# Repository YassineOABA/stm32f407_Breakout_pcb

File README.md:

# stm32f407_Breakout_pcb
HW PCB design based on STM32F407

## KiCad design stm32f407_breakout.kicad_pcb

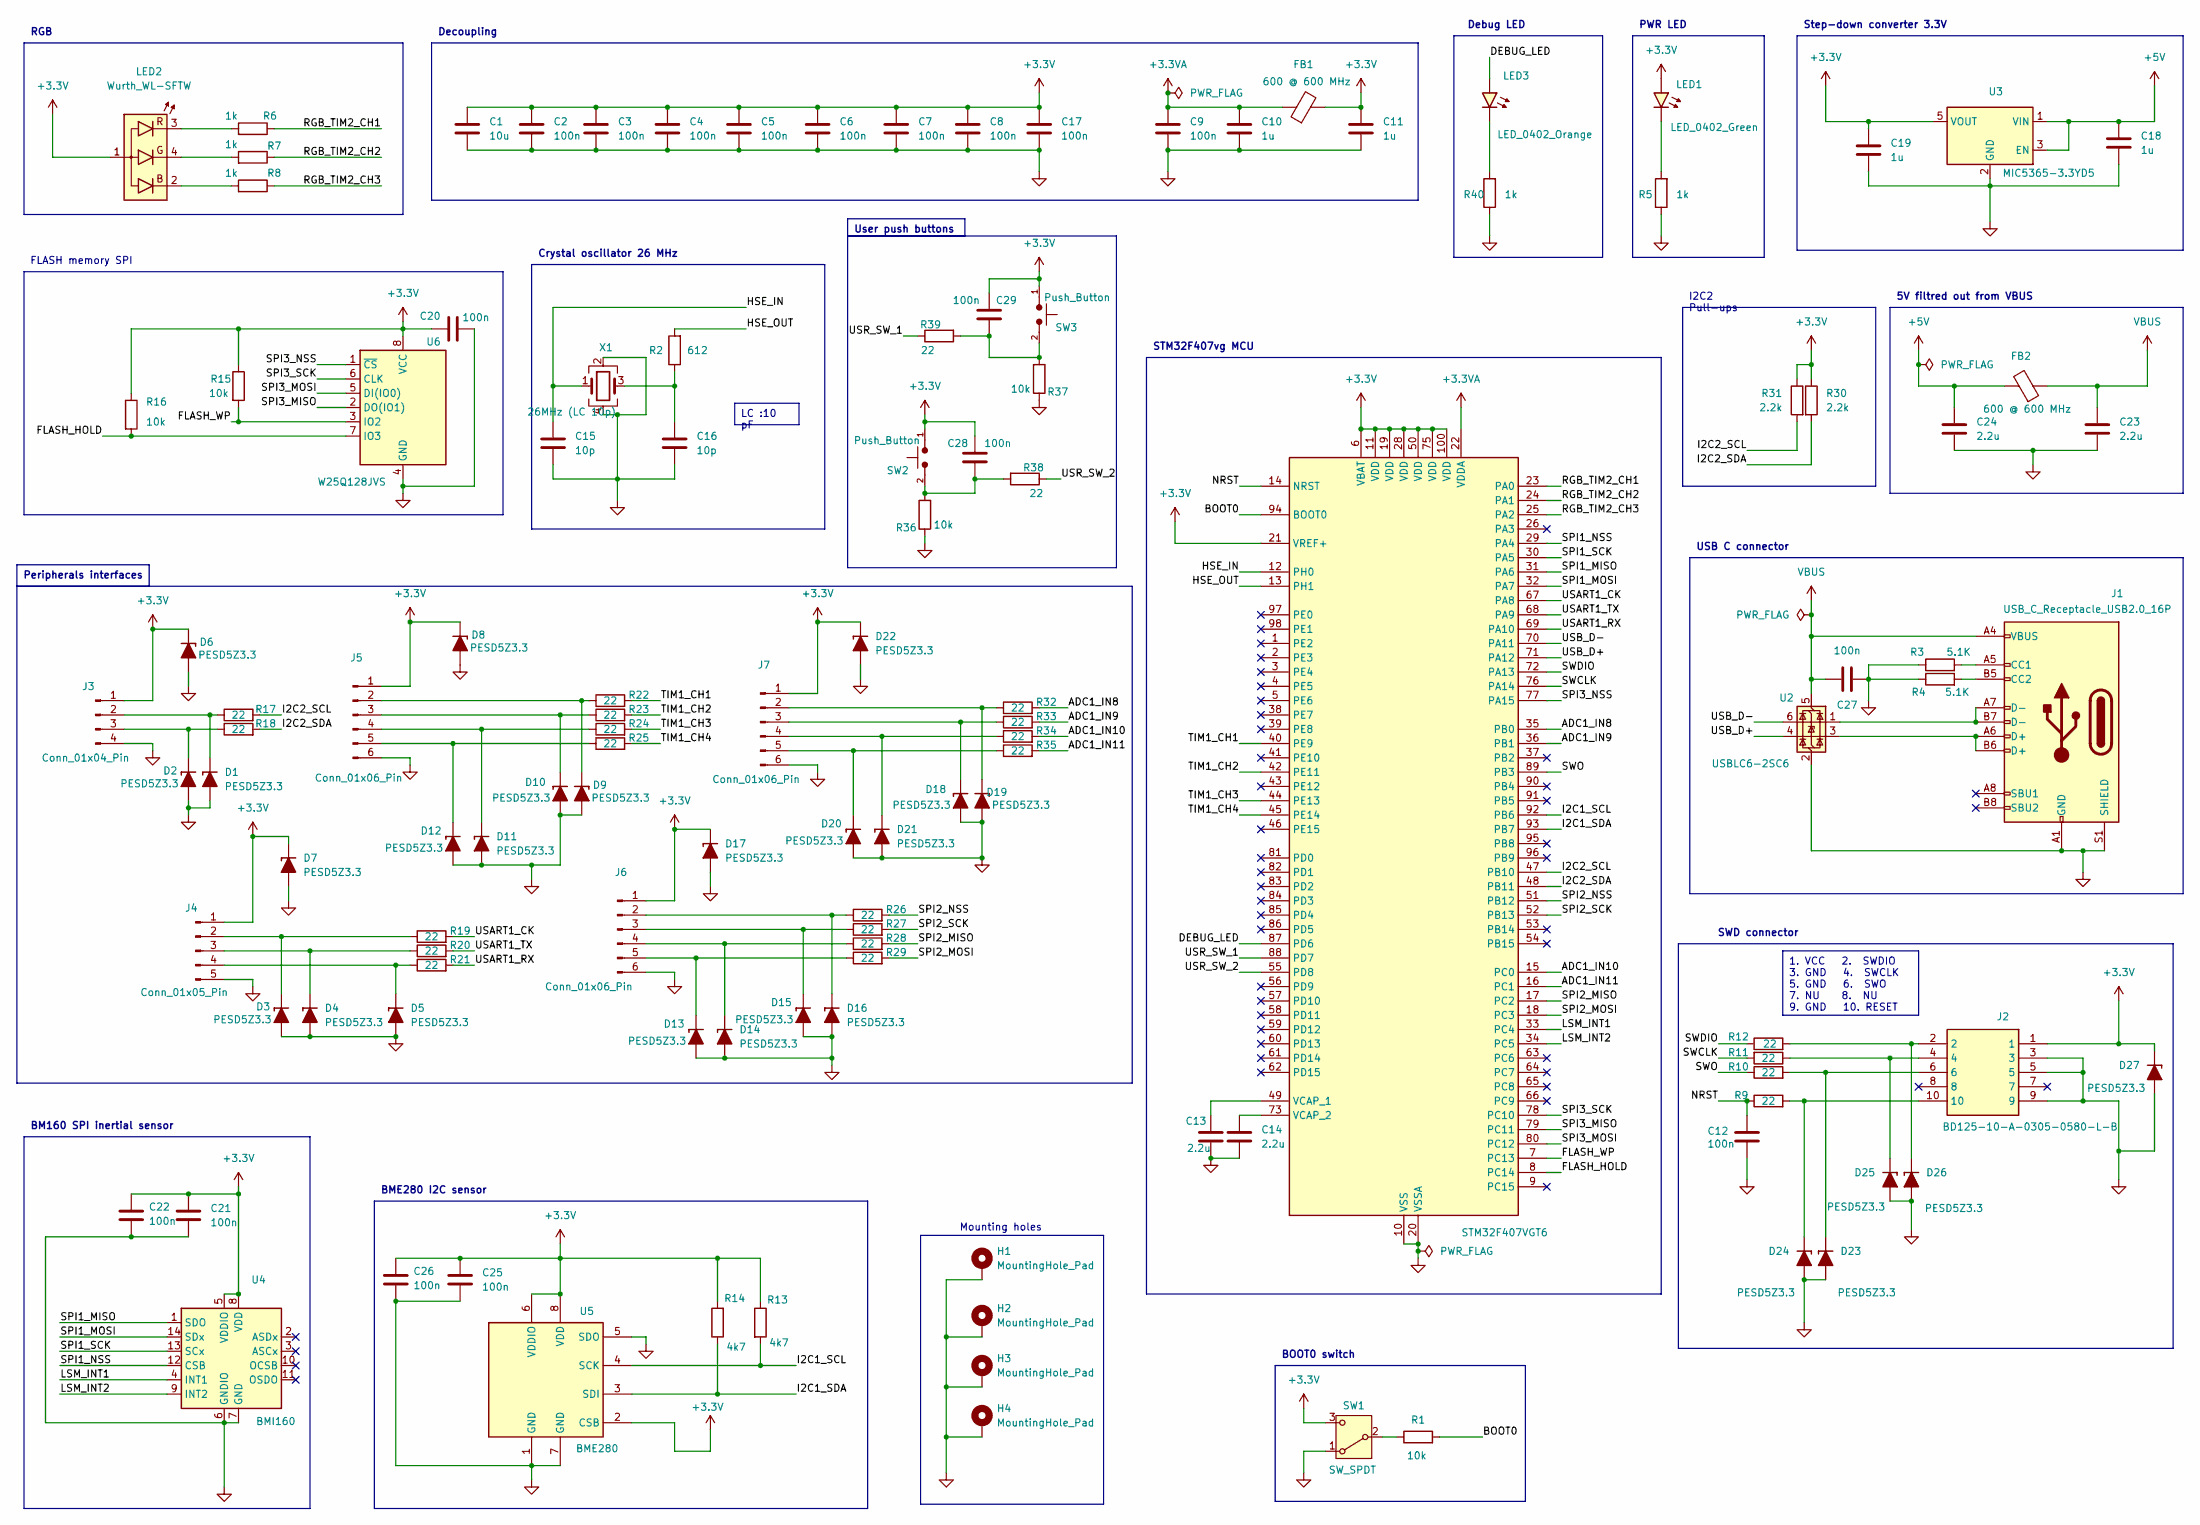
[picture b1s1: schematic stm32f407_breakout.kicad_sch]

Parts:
C1: 10u; C_0805_2012Metric
C2, C3, C4, C5, C6, C7, C8, C9, C12, C17, C20, C21, C22, C25, C26, C27: 100n; C_0402_1005Metric
C10, C11, C18, C19: 1u; C_0805_2012Metric
C13, C14, C23, C24: 2.2u; C_0805_2012Metric
C15, C16: 10p; C_0402_1005Metric
C28, C29: 100n; C_0805_2012Metric
D1, D2, D3, D4, D5, D6, D7, D8, D9, D10, D11, D12, D13, D14, D15, D16, D17, D18, D19, D20, D21, D22, D23, D24, D25, D26, D27: PESD5Z3.3; D_SOD-523
FB1, FB2: 600 @ 600 MHz; L_0603_1608Metric
H1, H2, H3, H4: MountingHole_Pad; MountingHole_2.2mm_M2_Pad_Via
J1: USB_C_Receptacle_USB2.0_16P; USB_C_Receptacle_GCT_USB4105-xx-A_16P_TopMnt_Horizontal
J2: BD125-10-A-0305-0580-L-B; BD12510A03050580LB; Mouser Part Number 640-BD12510A305580LB
J3: Conn_01x04_Pin; SolderWire-0.1sqmm_1x04_P3.6mm_D0.4mm_OD1mm
J4: Conn_01x05_Pin; SolderWire-0.1sqmm_1x05_P3.6mm_D0.4mm_OD1mm
J5, J6, J7: Conn_01x06_Pin; SolderWire-0.1sqmm_1x06_P3.6mm_D0.4mm_OD1mm
LED1: LED_0402_Green; LED_0402_1005Metric
LED2: Wurth_WL-SFTW; LED_RGB_Wuerth-PLCC4_3.2x2.8mm_150141M173100
LED3: LED_0402_Orange; LED_0402_1005Metric
R1, R15, R16, R36, R37: 10k; R_0402_1005Metric
R2: 612; R_0402_1005Metric
R3, R4: 5.1K; R_0402_1005Metric
R5, R6, R7, R8, R40: 1k; R_0402_1005Metric
R9, R10, R11, R12, R17, R18, R19, R20, R21, R22, R23, R24, R25, R26, R27, R28, R29, R32, R33, R34, R35, R38, R39: 22; R_0402_1005Metric
R13, R14: 4k7; R_0402_1005Metric
R30, R31: 2.2k; R_0402_1005Metric
SW1: SW_SPDT; SW_SPDT_PCM12
SW2, SW3: Push_Button; SW_SPST_PTS645
U1: STM32F407VGT6; LQFP-100_14x14mm_P0.5mm
U2: USBLC6-2SC6; SOT-23-6
U3: MIC5365-3.3YD5; SOT-23-5
U4: BMI160; Bosch_LGA-14_3x2.5mm_P0.5mm
U5: BME280; Bosch_LGA-8_2.5x2.5mm_P0.65mm_ClockwisePinNumbering
U6: W25Q128JVS; SOIC-8_5.23x5.23mm_P1.27mm
X1: 26MHz (LC 10p); Crystal_SMD_3225-4Pin_3.2x2.5mm

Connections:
+3.3V: C1.1, C2.1, C3.1, C4.1, C5.1, C6.1, C7.1, C8.1, C11.1, C17.1, C19.1, C20.2, C21.2, C22.2, C25.2, C26.2, C28.1, C29.1, D6.1 (K), D7.1 (K), D8.1 (K), D17.1 (K), D22.1 (K), D27.1 (K), FB1.2, J2.1, J3.1, J4.1, J5.1, J6.1, J7.1, LED1.2 (A), LED2.1 (A), R13.1, R14.2, R15.1, R16.1, R30.1, R31.1, SW1.3 (C), SW2.1, SW3.1, U1.6 (VBAT), U1.11 (VDD), U1.19 (VDD), U1.21 (VREF+), U1.28 (VDD), U1.50 (VDD), U1.75 (VDD), U1.100 (VDD), U3.5 (VOUT), U4.5 (VDDIO), U4.8 (VDD), U5.2 (CSB), U5.6 (VDDIO), U5.8 (VDD), U6.8 (VCC)
+3.3VA: C9.1, C10.1, FB1.1, U1.22 (VDDA)
+5V: C18.2, C24.2, FB2.2, U3.1 (VIN), U3.3 (EN)
/ADC1_IN8: R32.2, U1.35 (PB0)
/ADC1_IN9: R33.2, U1.36 (PB1)
/ADC1_IN10: R34.2, U1.15 (PC0)
/ADC1_IN11: R35.2, U1.16 (PC1)
/BOOT0: R1.2, U1.94 (BOOT0)
/DEBUG_LED: LED3.2 (A), U1.87 (PD6)
/FLASH_HOLD: R16.2, U1.8 (PC14), U6.7 (IO3)
/FLASH_WP: R15.2, U1.7 (PC13), U6.3 (IO2)
/HSE_IN: C15.1, U1.12 (PH0), X1.1
/HSE_OUT: R2.2, U1.13 (PH1)
/I2C1_SCL: R13.2, U1.92 (PB6), U5.4 (SCK)
/I2C1_SDA: R14.1, U1.93 (PB7), U5.3 (SDI)
/I2C2_SCL: R17.2, R31.2, U1.47 (PB10)
/I2C2_SDA: R18.2, R30.2, U1.48 (PB11)
/LSM_INT1: U1.33 (PC4), U4.4 (INT1)
/LSM_INT2: U1.34 (PC5), U4.9 (INT2)
/NRST: C12.1, R9.1, U1.14 (NRST)
/RGB_TIM2_CH1: R6.1, U1.23 (PA0)
/RGB_TIM2_CH2: R7.1, U1.24 (PA1)
/RGB_TIM2_CH3: R8.1, U1.25 (PA2)
/SPI1_MISO: U1.31 (PA6), U4.1 (SDO)
/SPI1_MOSI: U1.32 (PA7), U4.14 (SDx)
/SPI1_NSS: U1.29 (PA4), U4.12 (CSB)
/SPI1_SCK: U1.30 (PA5), U4.13 (SCx)
/SPI2_MISO: R28.2, U1.17 (PC2)
/SPI2_MOSI: R29.2, U1.18 (PC3)
/SPI2_NSS: R26.2, U1.51 (PB12)
/SPI2_SCK: R27.2, U1.52 (PB13)
/SPI3_MISO: U1.79 (PC11), U6.2 (DO(IO1))
/SPI3_MOSI: U1.80 (PC12), U6.5 (DI(IO0))
/SPI3_NSS: U1.77 (PA15), U6.1 (~CS)
/SPI3_SCK: U1.78 (PC10), U6.6 (CLK)
/SWCLK: R11.2, U1.76 (PA14)
/SWDIO: R12.1, U1.72 (PA13)
/SWO: R10.1, U1.89 (PB3)
/TIM1_CH1: R22.2, U1.40 (PE9)
/TIM1_CH2: R23.2, U1.42 (PE11)
/TIM1_CH3: R24.2, U1.44 (PE13)
/TIM1_CH4: R25.2, U1.45 (PE14)
/USART1_CK: R19.2, U1.67 (PA8)
/USART1_RX: R21.2, U1.69 (PA10)
/USART1_TX: R20.2, U1.68 (PA9)
/USB_D+: U1.71 (PA12), U2.4 (I/O2)
/USB_D-: U1.70 (PA11), U2.6 (I/O1)
/USR_SW_1: R39.1, U1.88 (PD7)
/USR_SW_2: R38.1, U1.55 (PD8)
GND: C1.2, C2.2, C3.2, C4.2, C5.2, C6.2, C7.2, C8.2, C9.2, C10.2, C11.2, C12.2, C13.1, C14.2, C15.2, C16.2, C17.2, C18.1, C19.2, C20.1, C21.1, C22.1, C23.2, C24.1, C25.1, C26.1, C27.1, D1.2 (A), D2.2 (A), D3.2 (A), D4.2 (A), D5.2 (A), D6.2 (A), D7.2 (A), D8.2 (A), D9.2 (A), D10.2 (A), D11.2 (A), D12.2 (A), D13.2 (A), D14.2 (A), D15.2 (A), D16.2 (A), D17.2 (A), D18.2 (A), D19.2 (A), D20.2 (A), D21.2 (A), D22.2 (A), D23.2 (A), D24.2 (A), D25.2 (A), D26.2 (A), D27.2 (A), H1.1, H2.1, H3.1, H4.1, J1.A1 (GND), J1.A12 (GND), J1.B1 (GND), J1.B12 (GND), J1.S1 (SHIELD), J2.3, J2.5, J2.9, J3.4, J4.5, J5.6, J6.6, J7.6, R3.1, R4.1, R5.1, R36.1, R37.1, R40.1, SW1.1 (A), U1.10 (VSS), U1.20 (VSSA), U1.27 (VSS), U1.74 (VSS), U1.99 (VSS), U2.2 (GND), U3.2 (GND), U4.6 (GNDIO), U4.7 (GND), U5.1 (GND), U5.5 (SDO), U5.7 (GND), U6.4 (GND), X1.2, X1.4
unnamed: C16.1, R2.1, X1.3
unnamed: C28.2, R36.2, R38.2, SW2.2
unnamed: C29.2, R37.2, R39.2, SW3.2
unnamed: D1.1 (K), J3.2, R17.1
unnamed: D2.1 (K), J3.3, R18.1
unnamed: D3.1 (K), J4.2, R19.1
unnamed: D4.1 (K), J4.3, R20.1
unnamed: D5.1 (K), J4.4, R21.1
unnamed: D9.1 (K), J5.2, R22.1
unnamed: D10.1 (K), J5.3, R23.1
unnamed: D11.1 (K), J5.4, R24.1
unnamed: D12.1 (K), J5.5, R25.1
unnamed: D13.1 (K), J6.5, R29.1
unnamed: D14.1 (K), J6.4, R28.1
unnamed: D15.1 (K), J6.3, R27.1
unnamed: D16.1 (K), J6.2, R26.1
unnamed: D18.1 (K), J7.3, R33.1
unnamed: D19.1 (K), J7.2, R32.1
unnamed: D20.1 (K), J7.5, R35.1
unnamed: D21.1 (K), J7.4, R34.1
unnamed: D23.1 (K), J2.6, R10.2
unnamed: D24.1 (K), J2.10, R9.2
unnamed: D25.1 (K), J2.4, R11.1
unnamed: D26.1 (K), J2.2, R12.2
unnamed: J1.A5 (CC1), R3.2
unnamed: J1.B5 (CC2), R4.2
unnamed: J1.A6 (D+), J1.B6 (D+), U2.3 (I/O2)
unnamed: J1.A7 (D-), J1.B7 (D-), U2.1 (I/O1)
unnamed: LED1.1 (K), R5.2
unnamed: LED2.2 (B), R8.2
unnamed: LED2.4 (G), R7.2
unnamed: LED2.3 (R), R6.2
unnamed: LED3.1 (K), R40.2
unnamed: R1.1, SW1.2 (B)
unnamed: C13.2, U1.49 (VCAP_1)
unnamed: C14.1, U1.73 (VCAP_2)
VBUS: C23.1, C27.2, FB2.1, J1.A4 (VBUS), J1.A9 (VBUS), J1.B4 (VBUS), J1.B9 (VBUS), U2.5 (VBUS)

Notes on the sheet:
SWD connector
BOOT0 switch
BME280 I2C sensor
FLASH memory SPI
Crystal oscillator 26 MHz
RGB
Mounting holes
1. VCC 2. SWDIO 3. GND 4. SWCLK 5. GND 6. SWO 7. NU 8. NU 9. GND 10. RESET
User push buttons
5V filtred out from VBUS
Step-down converter 3.3V
STM32F407vg MCU
I2C2 Pull-ups
Peripherals interfaces
BM160 SPI inertial sensor
USB C connector
Decoupling
LC :10 pF
PWR LED
Debug LED

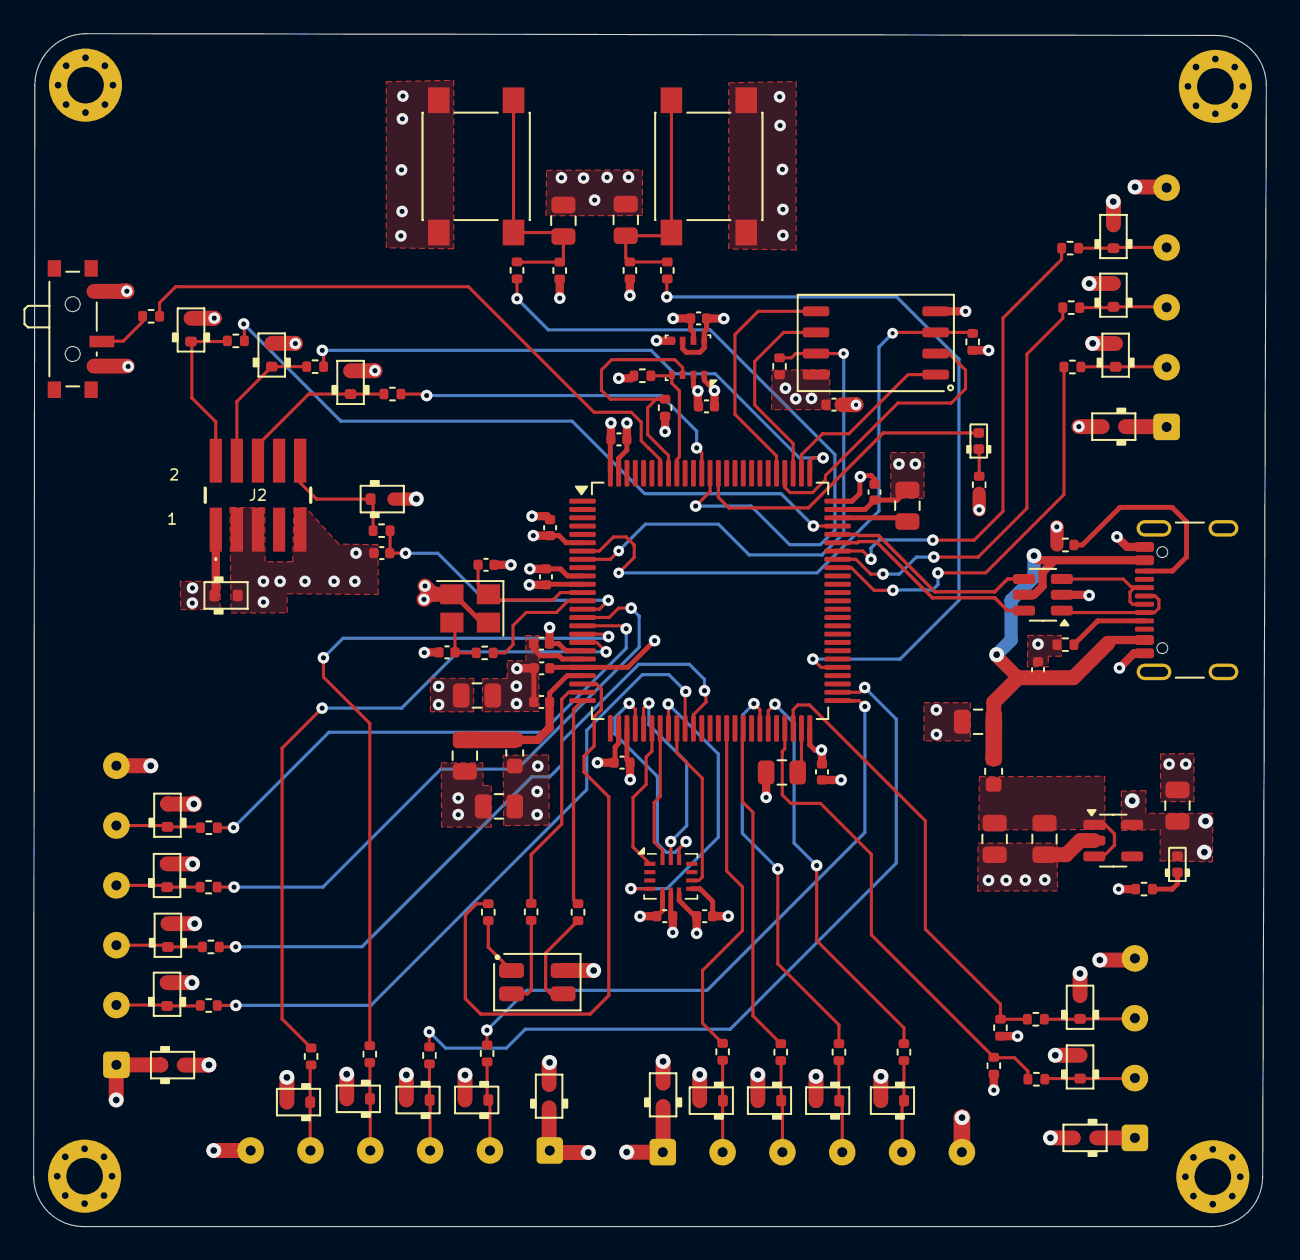
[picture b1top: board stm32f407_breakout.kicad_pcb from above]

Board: 4 copper layers, 74.2 x 71.8 mm, 122 parts (0 on the bottom side), 87 nets.

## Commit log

2025-01-16 STM32F407 breakout board design Kicad
2025-06-25 Add Board photos
2025-11-09 Add jpeg files
2025-11-09 remove unwanted files
